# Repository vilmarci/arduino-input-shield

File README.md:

This is my first try to create a 64 bit input shield for Arduino.

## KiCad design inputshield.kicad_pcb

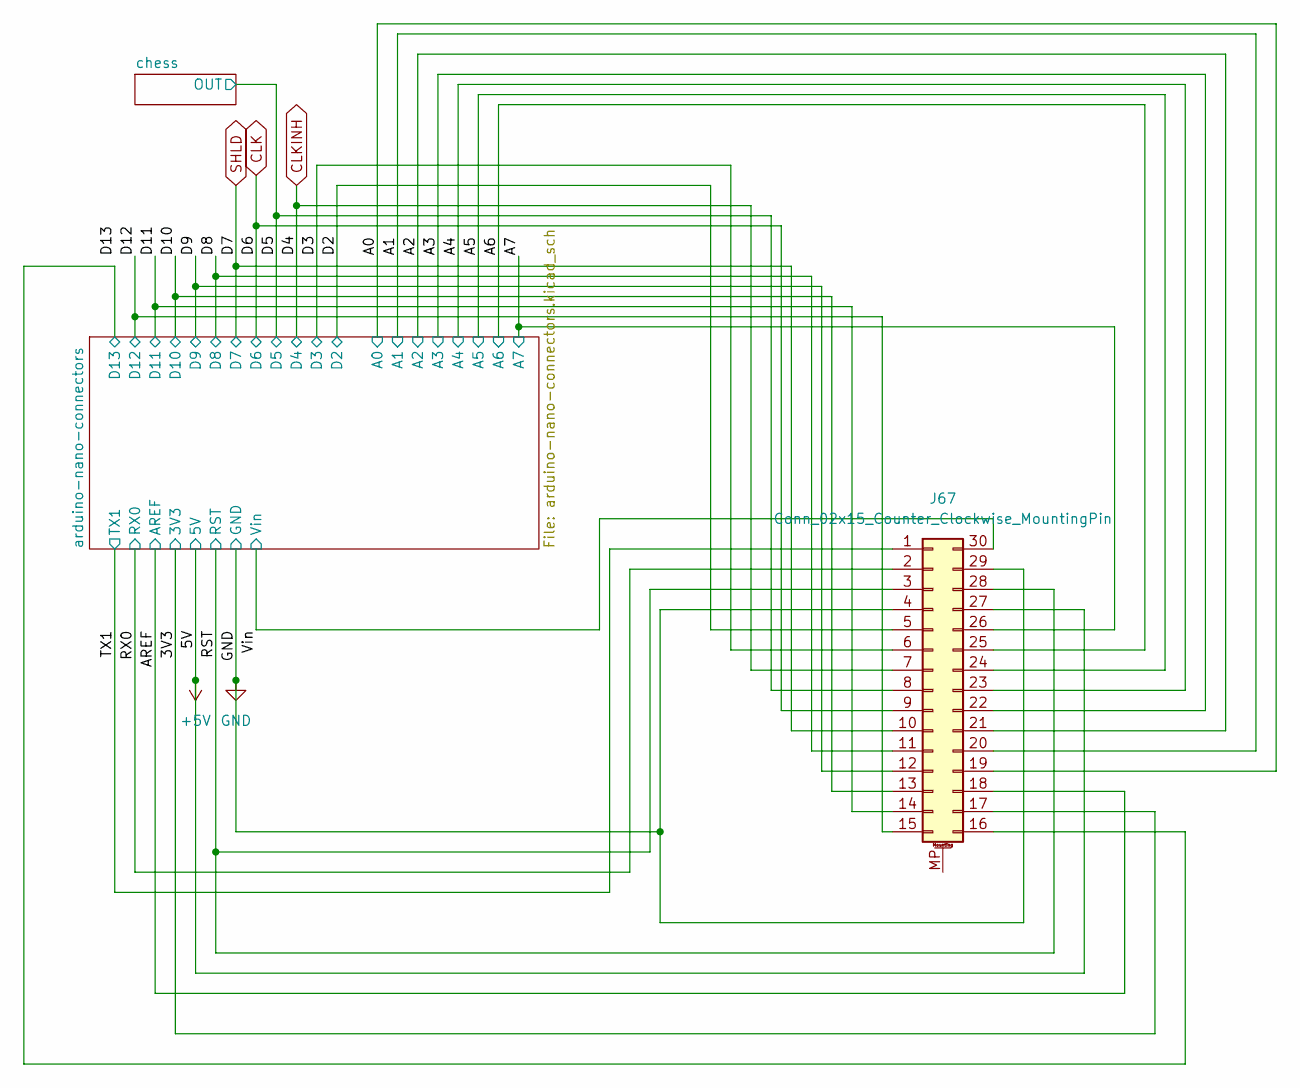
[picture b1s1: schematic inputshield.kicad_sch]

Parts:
J67: Conn_02x15_Counter_Clockwise_MountingPin; IDC-Header_2x15-1MP_P2.54mm_Latch6.5mm_Vertical

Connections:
+5V: J67.27; also elsewhere on the board
/3V3: J67.17; also elsewhere on the board
/A0: J67.19; also elsewhere on the board
/A1: J67.20; also elsewhere on the board
/A2: J67.21; also elsewhere on the board
/A3: J67.22; also elsewhere on the board
/A4: J67.23; also elsewhere on the board
/A5: J67.24; also elsewhere on the board
/A6: J67.25; also elsewhere on the board
/A7: J67.26; also elsewhere on the board
/AREF: J67.18; also elsewhere on the board
/D2: J67.5; also elsewhere on the board
/D3: J67.6; also elsewhere on the board
/D5: J67.8; also elsewhere on the board
/D8: J67.11; also elsewhere on the board
/D9: J67.12; also elsewhere on the board
/D10: J67.13; also elsewhere on the board
/D11: J67.14; also elsewhere on the board
/D12: J67.15; also elsewhere on the board
/RST: J67.3, J67.28; also elsewhere on the board
/RX0: J67.2; also elsewhere on the board
/TX1: J67.1; also elsewhere on the board
/Vin: J67.30; also elsewhere on the board
/arduino-nano-connectors/D13: J67.16; also elsewhere on the board
CLK: J67.9; also elsewhere on the board
CLKINH: J67.7; also elsewhere on the board
GND: J67.4, J67.29; also elsewhere on the board
SHLD: J67.10; also elsewhere on the board

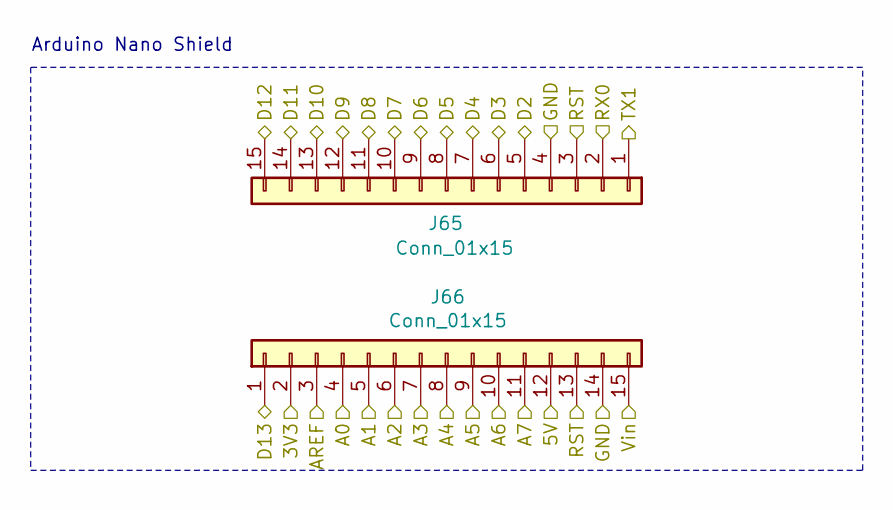
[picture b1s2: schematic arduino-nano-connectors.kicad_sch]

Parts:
J65, J66: Conn_01x15; PinSocket_1x15_P2.54mm_Vertical

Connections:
+5V: J66.12; also elsewhere on the board
/3V3: J66.2; also elsewhere on the board
/A0: J66.4; also elsewhere on the board
/A1: J66.5; also elsewhere on the board
/A2: J66.6; also elsewhere on the board
/A3: J66.7; also elsewhere on the board
/A4: J66.8; also elsewhere on the board
/A5: J66.9; also elsewhere on the board
/A6: J66.10; also elsewhere on the board
/A7: J66.11; also elsewhere on the board
/AREF: J66.3; also elsewhere on the board
/D2: J65.5; also elsewhere on the board
/D3: J65.6; also elsewhere on the board
/D5: J65.8; also elsewhere on the board
/D8: J65.11; also elsewhere on the board
/D9: J65.12; also elsewhere on the board
/D10: J65.13; also elsewhere on the board
/D11: J65.14; also elsewhere on the board
/D12: J65.15; also elsewhere on the board
/RST: J65.3, J66.13; also elsewhere on the board
/RX0: J65.2; also elsewhere on the board
/TX1: J65.1; also elsewhere on the board
/Vin: J66.15; also elsewhere on the board
/arduino-nano-connectors/D13: J66.1; also elsewhere on the board
CLK: J65.9; also elsewhere on the board
CLKINH: J65.7; also elsewhere on the board
GND: J65.4, J66.14; also elsewhere on the board
SHLD: J65.10; also elsewhere on the board

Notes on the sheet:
Arduino Nano Shield

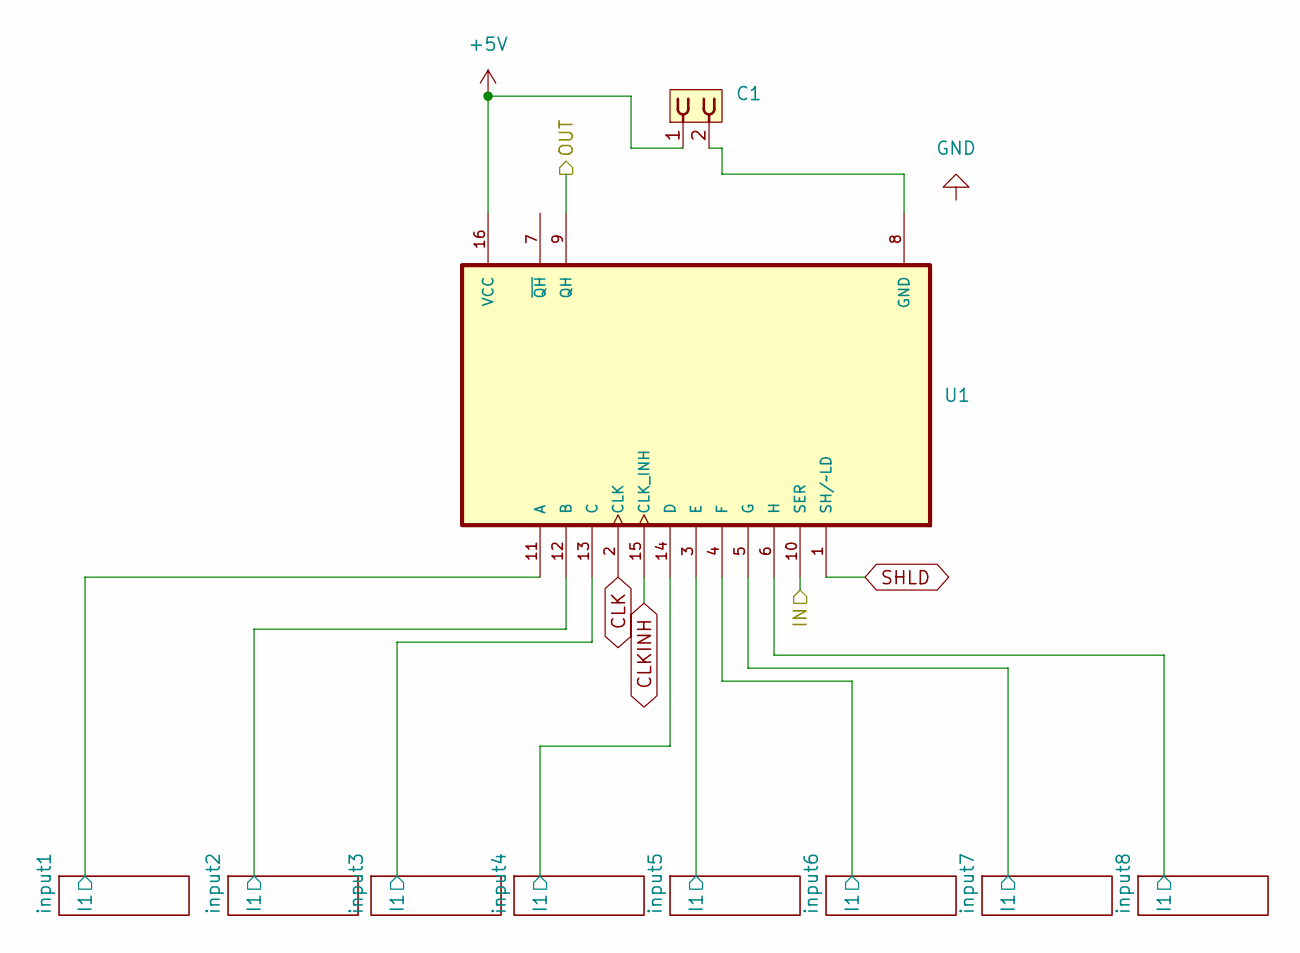
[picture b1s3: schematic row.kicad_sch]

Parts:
C1: PINHD_1x2_Female; PinSocket_1x02_P2.54mm_Vertical
U1: SN74HC165N; DIP794W45P254L1969H508Q16

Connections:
+5V: C1.1, U1.16 (VCC); also elsewhere on the board
/chess/row1/IN: U1.10 (SER)
/chess/row1/OUT: U1.9 (QH); also elsewhere on the board
/chess/row1/input1/I1: U1.11 (A); also elsewhere on the board
/chess/row1/input2/I1: U1.12 (B); also elsewhere on the board
/chess/row1/input3/I1: U1.13 (C); also elsewhere on the board
/chess/row1/input4/I1: U1.14 (D); also elsewhere on the board
/chess/row1/input5/I1: U1.3 (E); also elsewhere on the board
/chess/row1/input6/I1: U1.4 (F); also elsewhere on the board
/chess/row1/input7/I1: U1.5 (G); also elsewhere on the board
/chess/row1/input8/I1: U1.6 (H); also elsewhere on the board
CLK: U1.2 (CLK); also elsewhere on the board
CLKINH: U1.15 (CLK_INH); also elsewhere on the board
unnamed: C1.2, U1.8 (GND)
SHLD: U1.1 (SH/~LD); also elsewhere on the board

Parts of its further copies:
C2, C3, C4, C5, C6, C7, C8: PINHD_1x2_Female; PinSocket_1x02_P2.54mm_Vertical
U2, U3, U4, U5, U6, U7, U8: SN74HC165N; DIP794W45P254L1969H508Q16

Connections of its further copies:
+5V: C2.1, C3.1, C4.1, C5.1, C6.1, C7.1, C8.1, U2.16 (VCC), U3.16 (VCC), U4.16 (VCC), U5.16 (VCC), U6.16 (VCC), U7.16 (VCC), U8.16 (VCC); also elsewhere on the board
/D5: U8.9 (QH); also elsewhere on the board
/chess/row1/OUT: U2.10 (SER); also elsewhere on the board
/chess/row2/OUT: U2.9 (QH), U3.10 (SER)
/chess/row2/input1/I1: U2.11 (A); also elsewhere on the board
/chess/row2/input2/I1: U2.12 (B); also elsewhere on the board
/chess/row2/input3/I1: U2.13 (C); also elsewhere on the board
/chess/row2/input4/I1: U2.14 (D); also elsewhere on the board
/chess/row2/input5/I1: U2.3 (E); also elsewhere on the board
/chess/row2/input6/I1: U2.4 (F); also elsewhere on the board
/chess/row2/input7/I1: U2.5 (G); also elsewhere on the board
/chess/row2/input8/I1: U2.6 (H); also elsewhere on the board
/chess/row3/OUT: U3.9 (QH), U4.10 (SER)
/chess/row3/input1/I1: U3.11 (A); also elsewhere on the board
/chess/row3/input2/I1: U3.12 (B); also elsewhere on the board
/chess/row3/input3/I1: U3.13 (C); also elsewhere on the board
/chess/row3/input4/I1: U3.14 (D); also elsewhere on the board
/chess/row3/input5/I1: U3.3 (E); also elsewhere on the board
/chess/row3/input6/I1: U3.4 (F); also elsewhere on the board
/chess/row3/input7/I1: U3.5 (G); also elsewhere on the board
/chess/row3/input8/I1: U3.6 (H); also elsewhere on the board
/chess/row4/OUT: U4.9 (QH), U5.10 (SER)
/chess/row4/input1/I1: U4.11 (A); also elsewhere on the board
/chess/row4/input2/I1: U4.12 (B); also elsewhere on the board
/chess/row4/input3/I1: U4.13 (C); also elsewhere on the board
/chess/row4/input4/I1: U4.14 (D); also elsewhere on the board
/chess/row4/input5/I1: U4.3 (E); also elsewhere on the board
/chess/row4/input6/I1: U4.4 (F); also elsewhere on the board
/chess/row4/input7/I1: U4.5 (G); also elsewhere on the board
/chess/row4/input8/I1: U4.6 (H); also elsewhere on the board
/chess/row5/OUT: U5.9 (QH), U6.10 (SER)
/chess/row5/input1/I1: U5.11 (A); also elsewhere on the board
/chess/row5/input2/I1: U5.12 (B); also elsewhere on the board
/chess/row5/input3/I1: U5.13 (C); also elsewhere on the board
/chess/row5/input4/I1: U5.14 (D); also elsewhere on the board
/chess/row5/input5/I1: U5.3 (E); also elsewhere on the board
/chess/row5/input6/I1: U5.4 (F); also elsewhere on the board
/chess/row5/input7/I1: U5.5 (G); also elsewhere on the board
/chess/row5/input8/I1: U5.6 (H); also elsewhere on the board
/chess/row6/OUT: U6.9 (QH), U7.10 (SER)
/chess/row6/input1/I1: U6.11 (A); also elsewhere on the board
/chess/row6/input2/I1: U6.12 (B); also elsewhere on the board
/chess/row6/input3/I1: U6.13 (C); also elsewhere on the board
/chess/row6/input4/I1: U6.14 (D); also elsewhere on the board
/chess/row6/input5/I1: U6.3 (E); also elsewhere on the board
/chess/row6/input6/I1: U6.4 (F); also elsewhere on the board
/chess/row6/input7/I1: U6.5 (G); also elsewhere on the board
/chess/row6/input8/I1: U6.6 (H); also elsewhere on the board
/chess/row7/OUT: U7.9 (QH), U8.10 (SER)
/chess/row7/input1/I1: U7.11 (A); also elsewhere on the board
/chess/row7/input2/I1: U7.12 (B); also elsewhere on the board
/chess/row7/input3/I1: U7.13 (C); also elsewhere on the board
/chess/row7/input4/I1: U7.14 (D); also elsewhere on the board
/chess/row7/input5/I1: U7.3 (E); also elsewhere on the board
/chess/row7/input6/I1: U7.4 (F); also elsewhere on the board
/chess/row7/input7/I1: U7.5 (G); also elsewhere on the board
/chess/row7/input8/I1: U7.6 (H); also elsewhere on the board
/chess/row8/input1/I1: U8.11 (A); also elsewhere on the board
/chess/row8/input2/I1: U8.12 (B); also elsewhere on the board
/chess/row8/input3/I1: U8.13 (C); also elsewhere on the board
/chess/row8/input4/I1: U8.14 (D); also elsewhere on the board
/chess/row8/input5/I1: U8.3 (E); also elsewhere on the board
/chess/row8/input6/I1: U8.4 (F); also elsewhere on the board
/chess/row8/input7/I1: U8.5 (G); also elsewhere on the board
/chess/row8/input8/I1: U8.6 (H); also elsewhere on the board
CLK: U2.2 (CLK), U3.2 (CLK), U4.2 (CLK), U5.2 (CLK), U6.2 (CLK), U7.2 (CLK), U8.2 (CLK); also elsewhere on the board
CLKINH: U2.15 (CLK_INH), U3.15 (CLK_INH), U4.15 (CLK_INH), U5.15 (CLK_INH), U6.15 (CLK_INH), U7.15 (CLK_INH), U8.15 (CLK_INH); also elsewhere on the board
unnamed: C2.2, U2.8 (GND)
unnamed: C3.2, U3.8 (GND)
unnamed: C4.2, U4.8 (GND)
unnamed: C5.2, U5.8 (GND)
unnamed: C6.2, U6.8 (GND)
unnamed: C7.2, U7.8 (GND)
unnamed: C8.2, U8.8 (GND)
SHLD: U2.1 (SH/~LD), U3.1 (SH/~LD), U4.1 (SH/~LD), U5.1 (SH/~LD), U6.1 (SH/~LD), U7.1 (SH/~LD), U8.1 (SH/~LD); also elsewhere on the board

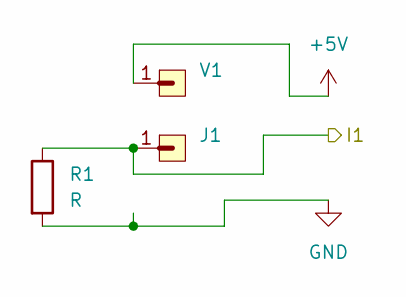
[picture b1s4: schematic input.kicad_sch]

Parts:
J1: PINHD_1x1_Male; PinHeader_1x01_P2.54mm_Vertical
R1: R; R_2816_7142Metric_Pad3.20x4.45mm_HandSolder
V1: PINHD_1x1_Male; PinHeader_1x01_P2.54mm_Vertical

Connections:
+5V: V1.1; also elsewhere on the board
/chess/row1/input1/I1: J1.1, R1.1; also elsewhere on the board
GND: R1.2; also elsewhere on the board

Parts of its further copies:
J2, J3, J4, J5, J6, J7, J8, J9, J10, J11, J12, J13, J14, J15, J16, J17, J18, J19, J20, J21, J22, J23, J24, J25, J26, J27, J28, J29, J30, J31, J32, J33, J34, J35, J36, J37, J38, J39, J40, J41, J42, J43, J44, J45, J46, J47, J48, J49, J50, J51, J52, J53, J54, J55, J56, J57, J58, J59, J60, J61, J62, J63, J64: PINHD_1x1_Male; PinHeader_1x01_P2.54mm_Vertical
R2, R3, R4, R5, R6, R7, R8, R9, R10, R11, R12, R13, R14, R15, R16, R17, R18, R19, R20, R21, R22, R23, R24, R25, R26, R27, R28, R29, R30, R31, R32, R33, R34, R35, R36, R37, R38, R39, R40, R41, R42, R43, R44, R45, R46, R47, R48, R49, R50, R51, R52, R53, R54, R55, R56, R57, R58, R59, R60, R61, R62, R63, R64: R; R_2816_7142Metric_Pad3.20x4.45mm_HandSolder
V2, V3, V4, V5, V6, V7, V8, V9, V10, V11, V12, V13, V14, V15, V16, V17, V18, V19, V20, V21, V22, V23, V24, V25, V26, V27, V28, V29, V30, V31, V32, V33, V34, V35, V36, V37, V38, V39, V40, V41, V42, V43, V44, V45, V46, V47, V48, V49, V50, V51, V52, V53, V54, V55, V56, V57, V58, V59, V60, V61, V62, V63, V64: PINHD_1x1_Male; PinHeader_1x01_P2.54mm_Vertical

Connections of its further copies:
+5V: V2.1, V3.1, V4.1, V5.1, V6.1, V7.1, V8.1, V9.1, V10.1, V11.1, V12.1, V13.1, V14.1, V15.1, V16.1, V17.1, V18.1, V19.1, V20.1, V21.1, V22.1, V23.1, V24.1, V25.1, V26.1, V27.1, V28.1, V29.1, V30.1, V31.1, V32.1, V33.1, V34.1, V35.1, V36.1, V37.1, V38.1, V39.1, V40.1, V41.1, V42.1, V43.1, V44.1, V45.1, V46.1, V47.1, V48.1, V49.1, V50.1, V51.1, V52.1, V53.1, V54.1, V55.1, V56.1, V57.1, V58.1, V59.1, V60.1, V61.1, V62.1, V63.1, V64.1; also elsewhere on the board
/chess/row1/input2/I1: J2.1, R2.1; also elsewhere on the board
/chess/row1/input3/I1: J3.1, R3.1; also elsewhere on the board
/chess/row1/input4/I1: J4.1, R4.1; also elsewhere on the board
/chess/row1/input5/I1: J5.1, R5.1; also elsewhere on the board
/chess/row1/input6/I1: J6.1, R6.1; also elsewhere on the board
/chess/row1/input7/I1: J7.1, R7.1; also elsewhere on the board
/chess/row1/input8/I1: J8.1, R8.1; also elsewhere on the board
/chess/row2/input1/I1: J9.1, R9.1; also elsewhere on the board
/chess/row2/input2/I1: J10.1, R10.1; also elsewhere on the board
/chess/row2/input3/I1: J11.1, R11.1; also elsewhere on the board
/chess/row2/input4/I1: J12.1, R12.1; also elsewhere on the board
/chess/row2/input5/I1: J13.1, R13.1; also elsewhere on the board
/chess/row2/input6/I1: J14.1, R14.1; also elsewhere on the board
/chess/row2/input7/I1: J15.1, R15.1; also elsewhere on the board
/chess/row2/input8/I1: J16.1, R16.1; also elsewhere on the board
/chess/row3/input1/I1: J17.1, R17.1; also elsewhere on the board
/chess/row3/input2/I1: J18.1, R18.1; also elsewhere on the board
/chess/row3/input3/I1: J19.1, R19.1; also elsewhere on the board
/chess/row3/input4/I1: J20.1, R20.1; also elsewhere on the board
/chess/row3/input5/I1: J21.1, R21.1; also elsewhere on the board
/chess/row3/input6/I1: J22.1, R22.1; also elsewhere on the board
/chess/row3/input7/I1: J23.1, R23.1; also elsewhere on the board
/chess/row3/input8/I1: J24.1, R24.1; also elsewhere on the board
/chess/row4/input1/I1: J25.1, R25.1; also elsewhere on the board
/chess/row4/input2/I1: J26.1, R26.1; also elsewhere on the board
/chess/row4/input3/I1: J27.1, R27.1; also elsewhere on the board
/chess/row4/input4/I1: J28.1, R28.1; also elsewhere on the board
/chess/row4/input5/I1: J29.1, R29.1; also elsewhere on the board
/chess/row4/input6/I1: J30.1, R30.1; also elsewhere on the board
/chess/row4/input7/I1: J31.1, R31.1; also elsewhere on the board
/chess/row4/input8/I1: J32.1, R32.1; also elsewhere on the board
/chess/row5/input1/I1: J33.1, R33.1; also elsewhere on the board
/chess/row5/input2/I1: J34.1, R34.1; also elsewhere on the board
/chess/row5/input3/I1: J35.1, R35.1; also elsewhere on the board
/chess/row5/input4/I1: J36.1, R36.1; also elsewhere on the board
/chess/row5/input5/I1: J37.1, R37.1; also elsewhere on the board
/chess/row5/input6/I1: J38.1, R38.1; also elsewhere on the board
/chess/row5/input7/I1: J39.1, R39.1; also elsewhere on the board
/chess/row5/input8/I1: J40.1, R40.1; also elsewhere on the board
/chess/row6/input1/I1: J41.1, R41.1; also elsewhere on the board
/chess/row6/input2/I1: J42.1, R42.1; also elsewhere on the board
/chess/row6/input3/I1: J43.1, R43.1; also elsewhere on the board
/chess/row6/input4/I1: J44.1, R44.1; also elsewhere on the board
/chess/row6/input5/I1: J45.1, R45.1; also elsewhere on the board
/chess/row6/input6/I1: J46.1, R46.1; also elsewhere on the board
/chess/row6/input7/I1: J47.1, R47.1; also elsewhere on the board
/chess/row6/input8/I1: J48.1, R48.1; also elsewhere on the board
/chess/row7/input1/I1: J49.1, R49.1; also elsewhere on the board
/chess/row7/input2/I1: J50.1, R50.1; also elsewhere on the board
/chess/row7/input3/I1: J51.1, R51.1; also elsewhere on the board
/chess/row7/input4/I1: J52.1, R52.1; also elsewhere on the board
/chess/row7/input5/I1: J53.1, R53.1; also elsewhere on the board
/chess/row7/input6/I1: J54.1, R54.1; also elsewhere on the board
/chess/row7/input7/I1: J55.1, R55.1; also elsewhere on the board
/chess/row7/input8/I1: J56.1, R56.1; also elsewhere on the board
/chess/row8/input1/I1: J57.1, R57.1; also elsewhere on the board
/chess/row8/input2/I1: J58.1, R58.1; also elsewhere on the board
/chess/row8/input3/I1: J59.1, R59.1; also elsewhere on the board
/chess/row8/input4/I1: J60.1, R60.1; also elsewhere on the board
/chess/row8/input5/I1: J61.1, R61.1; also elsewhere on the board
/chess/row8/input6/I1: J62.1, R62.1; also elsewhere on the board
/chess/row8/input7/I1: J63.1, R63.1; also elsewhere on the board
/chess/row8/input8/I1: J64.1, R64.1; also elsewhere on the board
GND: R2.2, R3.2, R4.2, R5.2, R6.2, R7.2, R8.2, R9.2, R10.2, R11.2, R12.2, R13.2, R14.2, R15.2, R16.2, R17.2, R18.2, R19.2, R20.2, R21.2, R22.2, R23.2, R24.2, R25.2, R26.2, R27.2, R28.2, R29.2, R30.2, R31.2, R32.2, R33.2, R34.2, R35.2, R36.2, R37.2, R38.2, R39.2, R40.2, R41.2, R42.2, R43.2, R44.2, R45.2, R46.2, R47.2, R48.2, R49.2, R50.2, R51.2, R52.2, R53.2, R54.2, R55.2, R56.2, R57.2, R58.2, R59.2, R60.2, R61.2, R62.2, R63.2, R64.2; also elsewhere on the board

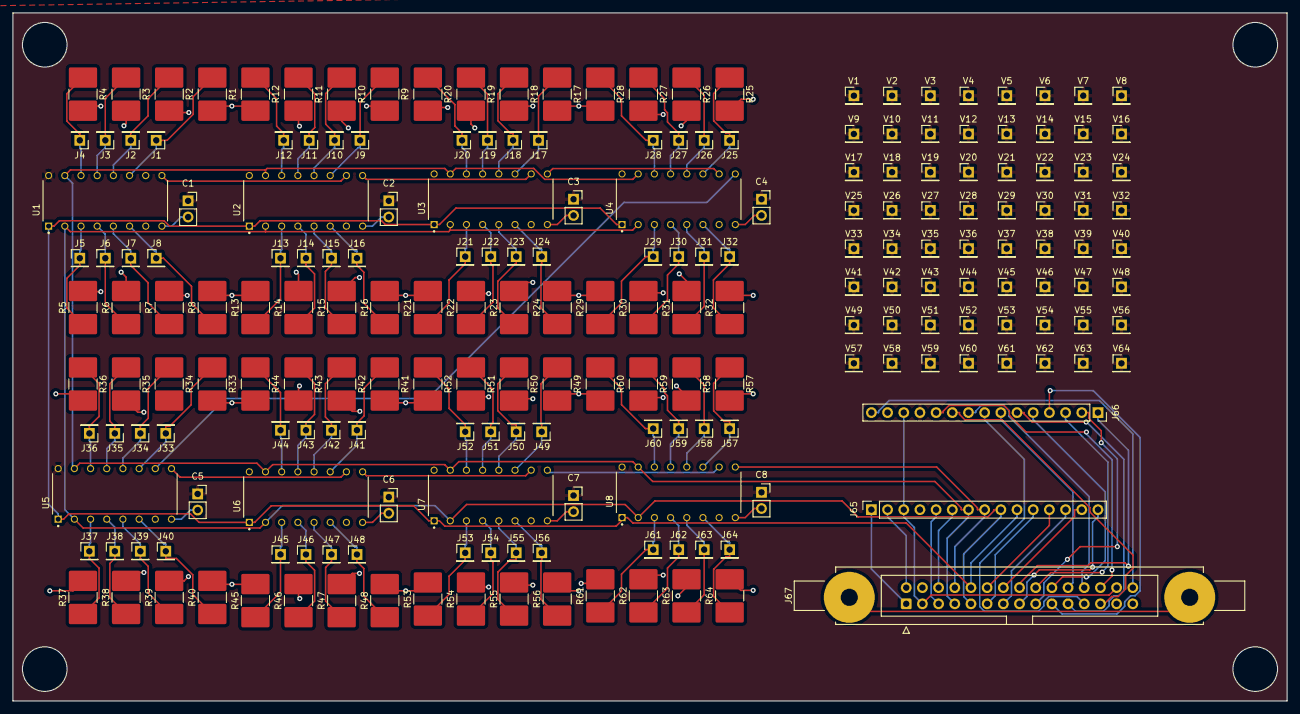
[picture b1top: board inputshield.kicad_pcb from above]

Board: 2 copper layers, 200.0 x 108.0 mm, 211 parts (0 on the bottom side), 107 nets.

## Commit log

2024-03-14 removing extra files
